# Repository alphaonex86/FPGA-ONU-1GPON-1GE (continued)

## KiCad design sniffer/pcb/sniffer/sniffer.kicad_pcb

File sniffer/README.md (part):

# GPON sniffer

A passive tap on one ONU's drop fibre: both directions of that ONU's GPON traffic,
filtered to what concerns it, dumped with the direction of every record. Simple and
cheap: one small card on the DE25-Nano 40-pin GPIO. Origin: `../common/sniffer/sniffer-GPON.jpg`.

Versus the FPGA ONU (operator, 2026-11-02): the ONU + OLT proxy of this repo sits in the path
and can intervene in the packets; the sniffer cannot touch anything, it only listens, but it
dumps without complications (no activation, no cloning, the stock ONU keeps its link).

## Decisions (operator, 2026-11-02)

- Customer side, not provider: the OLT is the ISP's, remote and out of our hands. The tap goes
  between the wall fibre outlet and our own ONU; the sniffer must stay invisible to the ISP
  (passive, never emits; our ONU receives about 4 dB less, see Coupler).
- The link: about 5 km of fibre from the ISP; our ONU reports
  -17 to -27 dBm received. -27 dBm is already at a class B+ ONU's sensitivity (-27/-28 dBm),
  so any optical tap that takes light from the downstream can drop our ONU off the PON.
  Range across installations: the sniffer is for homes at -23 dBm or better (Coupler).
- Tap: two 1x2 couplers back to back in our ONU's drop (Coupler below), so the two
  directions arrive on two fibres (no WDM) and the upstream holds our ONU's bursts only,
  at one constant power.
- Optics: two BOSAs, receive only. Downstream: an ONU BOSA RX (X100DG, 1490 nm, APD-TIA).
  Upstream: the OLT BOSA XL-BCB2111-LS-02 RX (1310 nm, 1.25 Gb/s APD-TIA, -32 dBm). Each
  into a SY88349NDL limiting amp. No laser driver is fitted: the sniffer cannot emit into
  the PON, by construction. SFP modules were dropped: no raw GPON ONU module without a MAC
  on AliExpress (only "sticks" with a MAC); raw ones exist at Optcore/FiberMall/PLANET.
- Platform: an ECP5 SerDes card on the DE25-Nano GPIO (the `../de25-nano/pcb` bridge
  plan; the operator owns a DE25-Nano). The ECP5 deserialises; the Agilex runs the existing GTC deframer, FEC, AES
  and the filter; the HPS writes the dump.

## Coupler (operator, 2026-11-02)

Two 1x2 back to back: wall - [common 1x2 #1 50 %] - [90 % 1x2 #2 common] - ONU. The free leg of #1
is the downstream copy, the 10 % leg of #2 the upstream copy (one 1x2 alone taps one direction:
the light entering a leg leaves by the common port). #1 is a 50:50, #2 a 90:10: the
operator has several of each (unbalanced 1x2 for building GPON networks).
- ONU: about 4 dB less (3.5 + 0.5). The -17 to -27 dBm range is across installations, so the
  sniffer fits a home whose ONU reports -23 dBm or better without the tap (it then stays at
  -27 dBm or better, a class B+ ONU's sensitivity).
- Downstream: the sniffer gets the ONU's tapped level + 0.5 dB, at least -26.5 dBm there, above
  the APD's -28 dBm.
- Upstream: the ONU emits +0.5 to +5 dBm, the sniffer sees about -10 to -5.5 dBm, near an APD's
  overload (-8 dBm typical for an OLT receiver): a 5 dB SC attenuator on the upstream tap fibre.

## DE25-Nano: verified (2026-11-02)

- GPIO headers are 3.3 V HVIO: 100 MHz SDR or 200 Mb/s DDR per pin (Altera Agilex 5 GPIO
  architecture brief); the HVIO clock input reaches the I/O PLL up to 156.25 MHz (data sheet).
- So the card sends DDR: DS 2.48832 Gb/s on 16 pins + US 1.24416 Gb/s on 8 pins, 155.52 Mb/s
  per pin (78 % of the limit) on a 77.76 MHz forwarded clock. With CCLK/MOSI/MISO/SN/PROGRAMN
  (slave-SPI configuration from the Agilex) and I2C: 36 of the 40 pins of GPIO_0.
- The Agilex A5EB013 is the DE25-Standard's density (138K LE), where the GTC/FEC/AES already
  meet timing; the HPS has the GbE port and the microSD for the dump.
- The two ECP5 bridge boards in `../de25-nano/pcb` send 155.52 MHz SDR: above the 100 MHz HVIO limit.

## Card (`pcb/sniffer`, generated by `../common/pcb/gen`)

Routed 2026-11-02: KRT, then close_opens on the last 5 nets; KiCad: 0 errors, 0 unconnected.

ECP5 LFE5UM-25F (as the bridge boards), SerDes RX only: CH0 downstream (CDR), CH1 upstream
(lock-to-reference on the 155.52 MHz VCXO, which the ECP5 locks to the downstream like the
ONU board, so each burst needs only a phase pick). Each BOSA: receive can only, into a
SY88349NDL burst-mode limiting amp (SD mode, auto reset, squelch), its own TPS61391 APD bias
(DAC trim from an AD5593R, which also reads both APD currents = optical power at the tap).
Upstream coupling 220 pF (tau 11 ns), downstream 100 nF.

## Filter (downstream; the upstream is already this ONU only)

The ONU is named by its serial number. From the PLOAMs: Assign_ONU-ID (serial ->
ONU-ID), Assign_Alloc-ID, Configure_Port-ID (OMCI); from OMCI: the GEM Port CTPs
(data Port-IDs). Kept: PLOAMs to that ONU-ID or broadcast, the BWmap entries of its
Alloc-IDs, the GEM frames of its Port-IDs.

## RTL (`../common/hw/spinal/pon/sniffer`, test `pon.sniffer.SnifferTest`)

Vendor-neutral SpinalHDL, one line byte per clock per direction; no AES in hardware.
- `SnifferDs` (311.04 MHz): the GTC deframer (FEC included), then the filter: PLOAMs to
  `onuId` or broadcast (all with `allPloams`), BWmap entries and GEM fragments by two
  4096-bit maps (Alloc-ID, Port-ID) the HPS writes. GEM stays ciphered; its record carries
  the crypto-counter, the software decrypts.
- `SnifferUs` (155.52 MHz): delimiter hunt on any bit alignment, descramble from the BIP,
  one record per burst until 8 squelched (zero) line bytes.
- `RecordWriter`: the record stream; a record is kept or dropped whole, a full data FIFO
  cuts its tail (flag bit 7); drop and truncation counters.

Record: `0xA0|kind`, flags, payload length (16 LE), time (64 LE), payload.

| kind | payload | flags |
|------|---------|-------|
| 0 PLOAM | 12 bytes | 0: bad CRC |
| 1 allocation | 7 bytes as on the line | 0: bad CRC |
| 2 GEM fragment | Port-ID 16, PLI 16, counter 48, data | 2..0: PTI, 3: cut, 4: first bytes only (dump rule) |
| 3 upstream burst | BIP, ONU-ID, Ind, allocations | 0: maxBytes reached, 1: filtered, 2: FEC parity left out |

A filtered burst (in-line box, dump rules: `DumpRules.scala`, `UsGemFilter`) ends with its line length (16 LE); a
GEM fragment a rule dropped or shortened keeps its header, the HEC field XORed with `0x1000 | payload bytes left`.
Of a run of idle GEM headers the last one stays, its HEC field XORed with `0x1000 | idle headers left out before it`
(none left out: unchanged).

ECP5 (`ecp5/`, `sh sniffer/ecp5/build.sh` -> `out/ecp5/sniffer.bit`, yosys + nextpnr + trellis):
`sniffer_ecp5.v` (DCU, resets, PLL, DDR pins) around `SnifferBridge` (test `pon.sniffer.SnifferBridgeTest`);
`gen.py` writes the DCU parameters and the LPF from the routed board. All in the VCXO's domain
(124.416 MHz, CH0's TX clock): CH1 is read there; the downstream crosses a 16-word FIFO whose
fill is the phase detector of the VCXO loop (PI every 132 us, sigma-delta on VCXO_PWM;
`ecp5/vcxo_loop_model.py`: locked to 0.5 word in 14 s from 10 ppm). Upstream: one sample per
pair, the centre of isolated 1- or 3-sample runs (an edge on a sample reads either bit).
Timing (speed 6): VCXO domain 135.6 MHz for 124.4, out 125 for 77.8, DS 255 for 124.4.

Still to write: the Agilex wrapper (DDR capture, x4 / x2 serialisers, time base, both
streams to the HPS).

## Dump

pcapng, one interface per direction (0 = downstream, 1 = upstream), hardware
timestamps; one packet per record.

## Open

- SY88349NDL stock (LCSC not reachable from here) and its SD level resistor (5.1k start).
- Lead order of the X100DG BOSA's RX can (to measure); XL-BCB2111 order from its drawing.
- XL-BCB2111 connector: SC/UPC in the title, SC/APC on the drawing.
- CH1 between bursts: with the line squelched the DCU sees LOS and its phase detector stops
  (`PDEN_SEL`); the 2x pick needs the DCO to stay on the reference frequency there, to measure.
- DCU bit order: the first received bit taken in D0 (as LiteICLink's 8b10b path); a reversed
  lane would show as a deframer that never syncs.
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
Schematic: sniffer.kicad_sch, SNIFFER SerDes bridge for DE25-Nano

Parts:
C1, C3, C6, C9, C24, C25, C30, C48, C49, C50, C51, C54, C57, C60, C63, C65, C71, C80, C87, C96: 10u; C_0603_1608Metric
C2, C4, C5, C7, C8, C10, C11: 22u; C_0805_2012Metric
C12, C13, C66, C67: 1u; C_0402_1005Metric
C14, C15, C16, C17, C18, C19, C20, C21, C22, C23, C26, C27, C28, C29, C31, C32, C33, C34, C35, C36, C37, C38, C39, C40, C41, C42, C43, C44, C45, C46, C47, C52, C53, C55, C56, C58, C59, C61, C62, C64, C68, C69, C70, C72, C73, C74, C75, C76, C77, C78, C79, C83, C84, C85, C86, C95, C104, C105: 100n; C_0402_1005Metric
C81, C82: 220p; C_0402_1005Metric
C88, C89, C97, C98: 100n; C_0603_1608Metric; MPN 100 V X7R
C90, C99: 220p; C_0603_1608Metric; MPN 100 V X7R
C91, C100: 10n; C_0402_1005Metric; MPN 100 V X7R
C92, C101: 2.2u; C_0603_1608Metric
C93, C94, C102, C103: 10p; C_0402_1005Metric
D1, D2: BAT46WJ; D_SOD-323F; MPN BAT46WJ (100 V)
FB1, FB2, FB3, FB4, FB5, FB6, FB7, FB8, FB9, FB10: 120R@100MHz; L_0603_1608Metric; MPN BLM18PG121SN1D
H1, H2: M3; MountingHole_3.2mm_M3
J1: DE25-Nano GPIO; PinSocket_2x20_P2.54mm_Vertical
J2: JTAG; PinHeader_1x06_P2.54mm_Vertical
L1, L2: 2.2u; L_Cenker_CKCS252012; MPN SLO252012F2R2MTT
L3, L4: 4.7u; L_Cenker_CKCS252012; MPN 4.7 uH, Isat >= 1 A, 2520
R1, R3: 100k; R_0402_1005Metric
R2, R4: 120k; R_0402_1005Metric
R5, R6, R7, R8, R9, R12, R13, R14, R20, R24: 4.7k; R_0402_1005Metric
R10, R15, R16, R28, R37, R43, R46: 10k; R_0402_1005Metric
R11, R26, R35: 1k; R_0402_1005Metric
R17, R18, R21, R22: 49.9; R_0402_1005Metric
R19, R23: 5.1k; R_0402_1005Metric
R25, R34: 100; R_0402_1005Metric
R27: 300k; R_0603_1608Metric
R29, R38: 20k; R_0402_1005Metric
R30, R39: 39k; R_0402_1005Metric
R31, R40: 10; R_0402_1005Metric
R32, R41: 1.5k; R_0402_1005Metric
R33, R42: 3.01k; R_0402_1005Metric
R36: 330k; R_0603_1608Metric
R44, R45: 2.2k; R_0402_1005Metric
RN1, RN2, RN3, RN4, RN5, RN6, RN7: 22; R_Array_Convex_4x0402; MPN 4D02WGJ0220TCE
U1, U2: TLV62569DBVR; SOT-23-5; MPN TLV62569DBVR
U3: TLV75525PDBVR; SOT-23-5; MPN TLV75525PDBVR
U4: LFE5UM-25F-6BG381C; Lattice_caBGA-381_17x17mm_Layout20x20_P0.8mm; MPN LFE5UM-25F-6BG381C
U5: BOSA GPON (X100DG), RX can only; BOSA_GPON
U6, U8: SY88349NDLMG; QFN-16-1EP_3x3mm_P0.5mm_EP1.7x1.7mm_ThermalVias; MPN SY88349NDLMG
U7: XL-BCB2111-LS-02, RX can only; BOSA_RX_TO46
U9, U10: TPS61391RTER; WQFN-16-1EP_3x3mm_P0.5mm_EP1.68x1.68mm_ThermalVias; MPN TPS61391RTER
U11: AD5593RBRUZ; TSSOP-16_4.4x5mm_P0.65mm; MPN AD5593RBRUZ
Y1: SiT3821 155.52 MHz; Oscillator_SMD_SiTime_SiT9121-6Pin_3.2x2.5mm; MPN SiT3821AI-2B2-33NB155.520000 (LVDS, +-5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

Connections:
+1V1: C7.1, C8.1, C14.1, C15.1, C16.1, C17.1, C18.1, C19.1, C20.1, C21.1, C22.1, C23.1, C24.1, C25.1, L1.2, R1.1, U4.H8 (VCC), U4.H9 (VCC), U4.H10 (VCC), U4.H11 (VCC), U4.H12 (VCC), U4.H13 (VCC), U4.J8 (VCC), U4.J13 (VCC), U4.K8 (VCC), U4.K13 (VCC), U4.L8 (VCC), U4.L13 (VCC), U4.M8 (VCC), U4.M13 (VCC), U4.N8 (VCC), U4.N9 (VCC), U4.N10 (VCC), U4.N11 (VCC), U4.N12 (VCC), U4.N13 (VCC)
+1V1_HRX: C58.1, C59.1, C60.1, FB4.2, U4.T8 (VCCHRX0_D0CH0), U4.T9 (VCCHRX1_D0CH1)
+1V1_HTX: C55.1, C56.1, C57.1, FB3.2, U4.T7 (VCCHTX0_D0CH0), U4.T10 (VCCHTX1_D0CH1)
+1V1_SD: C10.1, C11.1, FB2.1, FB3.1, FB4.1, L2.2, R3.1
+1V1_VCCA: C52.1, C53.1, C54.1, FB2.2, U4.T6 (VCCA0), U4.U6 (VCCA0)
+2V5: C13.1, FB1.1, FB5.1, U3.5 (OUT)
+2V5_AUX: C26.1, C27.1, C28.1, C29.1, C30.1, FB1.2, U4.F6 (VCCAUX), U4.F15 (VCCAUX), U4.P6 (VCCAUX), U4.P15 (VCCAUX)
+2V5_AUXA: C61.1, C62.1, C63.1, FB5.2, U4.V10 (VCCAUXA0), U4.V11 (VCCAUXA0)
+3V3: C3.1, C4.1, C5.1, C12.1, C31.1, C32.1, C33.1, C34.1, C35.1, C36.1, C37.1, C38.1, C39.1, C40.1, C41.1, C42.1, C43.1, C44.1, C45.1, C46.1, C47.1, C48.1, C49.1, C50.1, C51.1, C105.1, FB6.1, FB7.1, FB8.1, FB9.1, FB10.1, J1.29, J2.1, R5.2, R6.2, R7.2, R8.2, R9.2, R10.2, R11.2, R12.2, R13.2, R20.2, R24.2, R43.2, R44.2, R45.2, R46.2, U3.1 (IN), U3.3 (EN), U4.F9 (VCCIO0), U4.F10 (VCCIO0), U4.F11 (VCCIO1), U4.F12 (VCCIO1), U4.H6 (VCCIO7), U4.H7 (VCCIO7), U4.H14 (VCCIO2), U4.H15 (VCCIO2), U4.J6 (VCCIO7), U4.J15 (VCCIO2), U4.L6 (VCCIO6), U4.L7 (VCCIO6), U4.L14 (VCCIO3), U4.L15 (VCCIO3), U4.M6 (VCCIO6), U4.M15 (VCCIO3), U4.P9 (VCCIO8), U4.P10 (VCCIO8), U11.3 (V_{DD}), U11.9 (V_{LOGIC})
+3V3_DS_APD: C86.1, C87.1, FB9.2, L3.1, R31.1, U9.10 (VIN), U9.13 (EN)
+3V3_DS_APDA: C92.1, R31.2, U9.14 (AVCC), U9.15 (AVCC)
+3V3_DS_OPT: C68.1, C69.1, C70.1, C71.1, FB7.2, R19.2, U5.R2 (VCC), U6.5 (VCC), U6.13 (LOS/SD_SEL), U6.16 (VCC)
+3V3_US_APD: C95.1, C96.1, FB10.2, L4.1, R40.1, U10.10 (VIN), U10.13 (EN)
+3V3_US_APDA: C101.1, R40.2, U10.14 (AVCC), U10.15 (AVCC)
+3V3_US_OPT: C77.1, C78.1, C79.1, C80.1, FB8.2, R23.2, U7.1 (VCC), U8.5 (VCC), U8.13 (LOS/SD_SEL), U8.16 (VCC)
+3V3_XO: C64.1, C65.1, FB6.2, Y1.6 (VDD)
+5V: C1.1, C2.1, C6.1, C9.1, J1.11, U1.1 (EN), U1.4 (VIN), U2.1 (EN), U2.4 (VIN)
CCLK: J1.15, R11.1, U4.U3 (CCLK)
CFG0: R5.1, U4.U4 (CFG_0)
DDM_RESET: R43.1, U11.1 (~RESET)
DDM_VREF: C104.1, U11.8 (V_{REF})
DONE: R8.1, U4.Y3 (DONE)
DS0: J1.13, RN4.5 (R4.2)
DS0_S: RN4.4 (R4.1), U4.B12 (PT35A/PCLKT1_0)
DS1: J1.14, RN4.6 (R3.2)
DS1_S: RN4.3 (R3.1), U4.B11 (PT29A/PCLKT0_0)
DS2: J1.16, RN4.7 (R2.2)
DS2_S: RN4.2 (R2.1), U4.A11 (PT27B/PCLKC0_1)
DS3: J1.18, RN4.8 (R1.2)
DS3_S: RN4.1 (R1.1), U4.A10 (PT27A/PCLKT0_1)
DS4: J1.23, RN3.5 (R4.2)
DS4_S: RN3.4 (R4.1), U4.B9 (PT22A)
DS5: J1.27, RN3.6 (R3.2)
DS5_S: RN3.3 (R3.1), U4.A9 (PT24A/GR_PCLK0_1)
DS6: J1.28, RN3.7 (R2.2)
DS6_S: RN3.2 (R2.1), U4.A8 (PT18B)
DS7: J1.31, RN3.8 (R1.2)
DS7_S: RN3.1 (R1.1), U4.A7 (PT18A)
DS8: J1.32, RN2.5 (R4.2)
DS8_S: RN2.4 (R4.1), U4.A6 (PT4A)
DS9: J1.33, RN2.6 (R3.2)
DS9_S: RN2.3 (R3.1), U4.B5 (PL2C)
DS10: J1.34, RN2.7 (R2.2)
DS10_S: RN2.2 (R2.1), U4.A5 (PL2B)
DS11: J1.35, RN2.8 (R1.2)
DS11_S: RN2.1 (R1.1), U4.A4 (PL2A)
DS12: J1.36, RN1.5 (R4.2)
DS12_S: RN1.4 (R4.1), U4.B3 (PL5D)
DS13: J1.37, RN1.6 (R3.2)
DS13_S: RN1.3 (R3.1), U4.B2 (PL14C/VREF1_7)
DS14: J1.38, RN1.7 (R2.2)
DS14_S: RN1.2 (R2.1), U4.A2 (PL14A)
DS15: J1.39, RN1.8 (R1.2)
DS15_S: RN1.1 (R1.1), U4.B1 (PL14B)
DS_APD_ADJ: R29.2, U11.4 (IO0)
DS_APD_CAP: C91.1, U9.9 (CAP)
DS_APD_FB: R27.2, R28.1, R29.1, U9.12 (FB)
DS_APD_ISHORT: R30.1, U9.11 (ISHORT)
DS_APD_MON: C93.1, R32.1, U9.4 (MON1), U11.6 (IO2)
DS_APD_MON2: C94.1, R33.1, U9.3 (MON2)
DS_DIN_N: C73.2, R18.1, U6.4 (/DIN)
DS_DIN_P: C72.2, R17.1, U6.1 (DIN)
DS_HV_APD: C90.1, U5.R1 (VAPD), U9.5 (APD)
DS_HV_FILT: C89.1, R25.2, R26.1
DS_HV_MONIN: R26.2, U9.6 (MONIN)
DS_HV_OUT: C88.1, D1.1 (K), R25.1, R27.1
DS_HV_SW: D1.2 (A), L3.2, U9.8 (SW)
DS_LA_N: C76.1, U6.9 (/DOUT)
DS_LA_P: C75.1, U6.12 (DOUT)
DS_RX_N: C76.2, U4.Y6 (HDRXN0_D0CH0)
DS_RX_P: C75.2, U4.Y5 (HDRXP0_D0CH0)
DS_SD: R20.1, U4.U17 (PR47B), U6.7 (SD/LOS), U6.15 (JAM)
DS_SDLVL: R19.1, U6.14 (LOS/SDLVL)
DS_TIA_N: C73.1, U5.R4 (OUT-)
DS_TIA_P: C72.1, U5.R3 (OUT+)
DS_VREF: C74.1, R17.2, R18.2, U6.2 (VREF)
FB_1V1: R1.2, R2.1, U1.5 (FB)
FB_1V1_SD: R3.2, R4.1, U2.5 (FB)
FWD_CLK: J1.1, RN7.8 (R1.2)
FWD_CLK_S: RN7.1 (R1.1), U4.B19 (PT65B)
GND: C1.2, C2.2, C3.2, C4.2, C5.2, C6.2, C7.2, C8.2, C9.2, C10.2, C11.2, C12.2, C13.2, C14.2, C15.2, C16.2, C17.2, C18.2, C19.2, C20.2, C21.2, C22.2, C23.2, C24.2, C25.2, C26.2, C27.2, C28.2, C29.2, C30.2, C31.2, C32.2, C33.2, C34.2, C35.2, C36.2, C37.2, C38.2, C39.2, C40.2, C41.2, C42.2, C43.2, C44.2, C45.2, C46.2, C47.2, C48.2, C49.2, C50.2, C51.2, C52.2, C53.2, C54.2, C55.2, C56.2, C57.2, C58.2, C59.2, C60.2, C61.2, C62.2, C63.2, C64.2, C65.2, C66.2, C67.2, C68.2, C69.2, C70.2, C71.2, C74.2, C77.2, C78.2, C79.2, C80.2, C83.2, C86.2, C87.2, C88.2, C89.2, C90.2, C91.2, C92.2, C93.2, C94.2, C95.2, C96.2, C97.2, C98.2, C99.2, C100.2, C101.2, C102.2, C103.2, C104.2, C105.2, J1.12, J1.30, J2.6, R2.2, R4.2, R14.2, R28.2, R30.2, R32.2, R33.2, R37.2, R39.2, R41.2, R42.2, U1.2 (GND), U2.2 (GND), U3.2 (GND)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
HOLDN: R10.1, U4.R2 (PB15A/HOLDN/DI/BUSY/CSSPIN/CEN)
INITN: R7.1, U4.V3 (INITN)
MISO: J1.19, R46.1, U4.V2 (PB11A/D1/MISO/IO1)
MOSI: J1.17, U4.W2 (PB11B/D0/MOSI/IO0)
PROGRAMN: J1.20, R6.1, U4.W3 (PROGRAMN)
REFCLK_N: U4.Y12 (REFCLKN_D0), Y1.5 (OUT-)
REFCLK_P: U4.Y11 (REFCLKP_D0), Y1.4 (OUT+)
SCL: J1.21, R44.1, U11.16 (SCL)
SDA: J1.22, R45.1, U11.15 (SDA)
SN: J1.40, R9.1, U4.T2 (PB13A/SN/CSN)
SW_1V1: L1.1, U1.3 (SW)
SW_1V1_SD: L2.1, U2.3 (SW)
TCK: J2.2, R14.1, U4.T5 (TCK)
TDI: J2.3, R12.1, U4.R5 (TDI)
TDO: J2.4, U4.V4 (TDO)
TMS: J2.5, R13.1, U4.U5 (TMS)
US0: J1.2, RN6.5 (R4.2)
US0_S: RN6.4 (R4.1), U4.A19 (PT67A)
US1: J1.4, RN6.6 (R3.2)
US1_S: RN6.3 (R3.1), U4.A18 (PT65A)
US2: J1.5, RN6.7 (R2.2)
US2_S: RN6.2 (R2.1), U4.B17 (PT60A)
US3: J1.6, RN6.8 (R1.2)
US3_S: RN6.1 (R1.1), U4.A17 (PT62A)
US4: J1.7, RN5.5 (R4.2)
US4_S: RN5.4 (R4.1), U4.A16 (PT56A)
US5: J1.8, RN5.6 (R3.2)
US5_S: RN5.3 (R3.1), U4.B15 (PT51A)
US6: J1.9, RN5.7 (R2.2)
US6_S: RN5.2 (R2.1), U4.B13 (PT42A)
US7: J1.10, RN5.8 (R1.2)
US7_S: RN5.1 (R1.1), U4.A13 (PT40B)
US_APD_ADJ: R38.2, U11.5 (IO1)
US_APD_CAP: C100.1, U10.9 (CAP)
US_APD_FB: R36.2, R37.1, R38.1, U10.12 (FB)
US_APD_ISHORT: R39.1, U10.11 (ISHORT)
US_APD_MON: C102.1, R41.1, U10.4 (MON1), U11.7 (IO3)
US_APD_MON2: C103.1, R42.1, U10.3 (MON2)
US_DIN_N: C82.2, R22.1, U8.4 (/DIN)
US_DIN_P: C81.2, R21.1, U8.1 (DIN)
US_HV_APD: C99.1, U7.2 (VAPD), U10.5 (APD)
US_HV_FILT: C98.1, R34.2, R35.1
US_HV_MONIN: R35.2, U10.6 (MONIN)
US_HV_OUT: C97.1, D2.1 (K), R34.1, R36.1
US_HV_SW: D2.2 (A), L4.2, U10.8 (SW)
US_LA_N: C85.1, U8.9 (/DOUT)
US_LA_P: C84.1, U8.12 (DOUT)
US_RX_N: C85.2, U4.Y8 (HDRXN0_D0CH1)
US_RX_P: C84.2, U4.Y7 (HDRXP0_D0CH1)
US_SD: R24.1, U4.T17 (PR47D/LRC_GPLL0C_IN), U8.7 (SD/LOS), U8.15 (JAM)
US_SDLVL: R23.1, U8.14 (LOS/SDLVL)
US_TIA_N: C82.1, U7.3 (OUT-)
US_TIA_P: C81.1, U7.5 (OUT+)
US_VREF: C83.1, R21.2, R22.2, U8.2 (VREF)
VCXO_PWM: R15.1, U4.U16 (PR47C/LRC_GPLL0T_IN)
VCXO_RC: C66.1, R15.2, R16.1
VCXO_VC: C67.1, R16.2, Y1.1 (VIN)

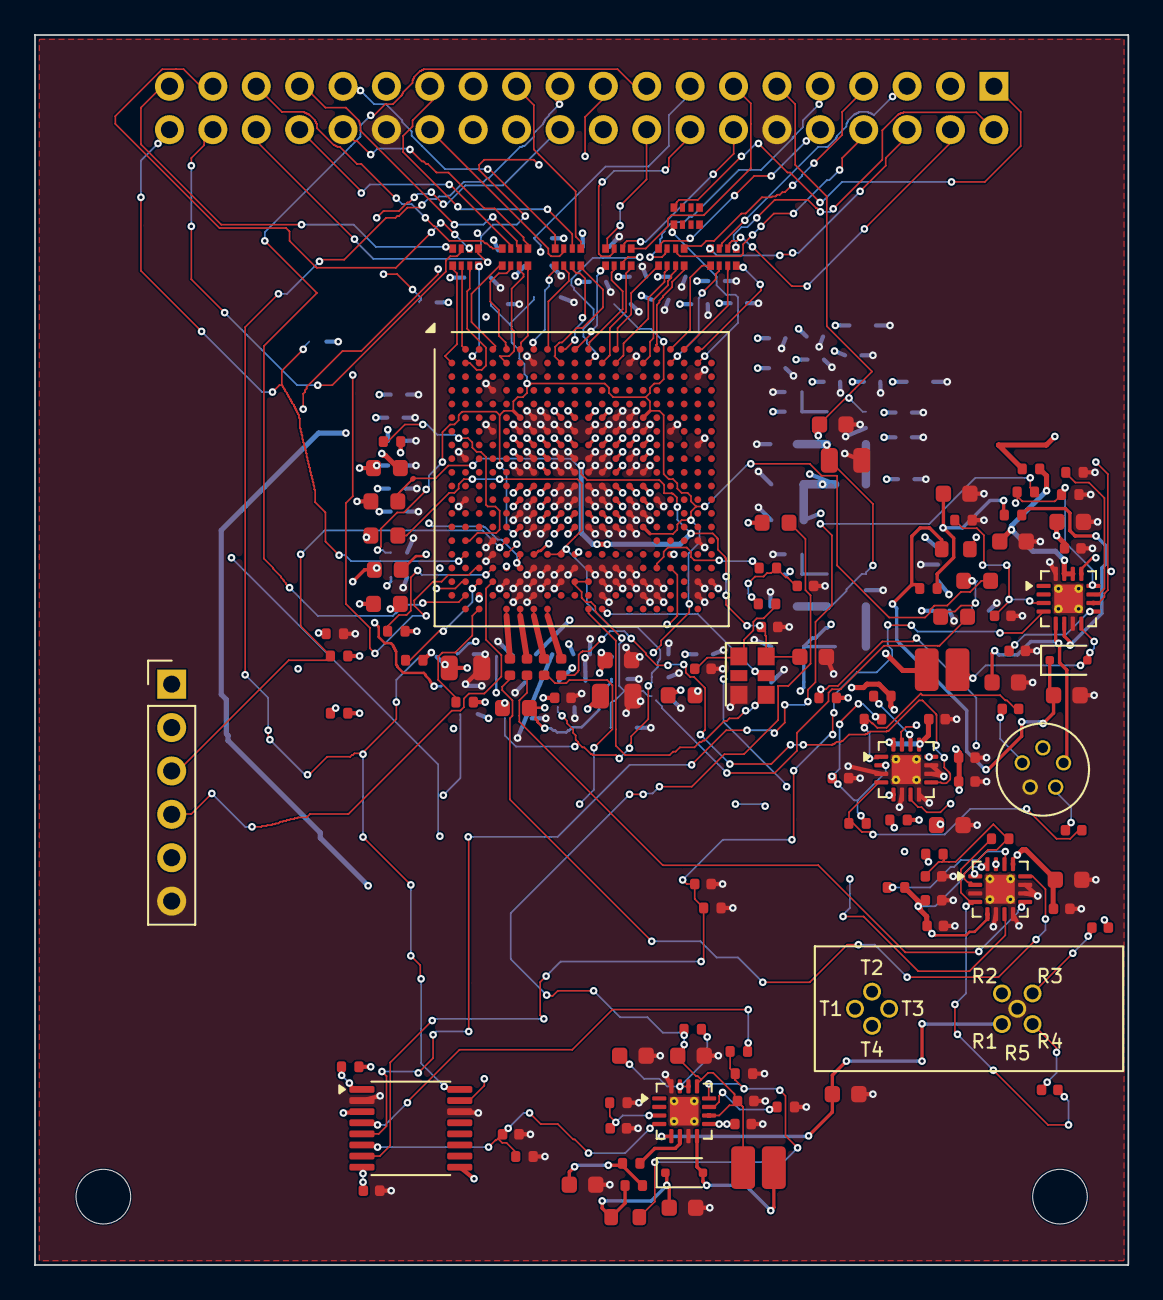
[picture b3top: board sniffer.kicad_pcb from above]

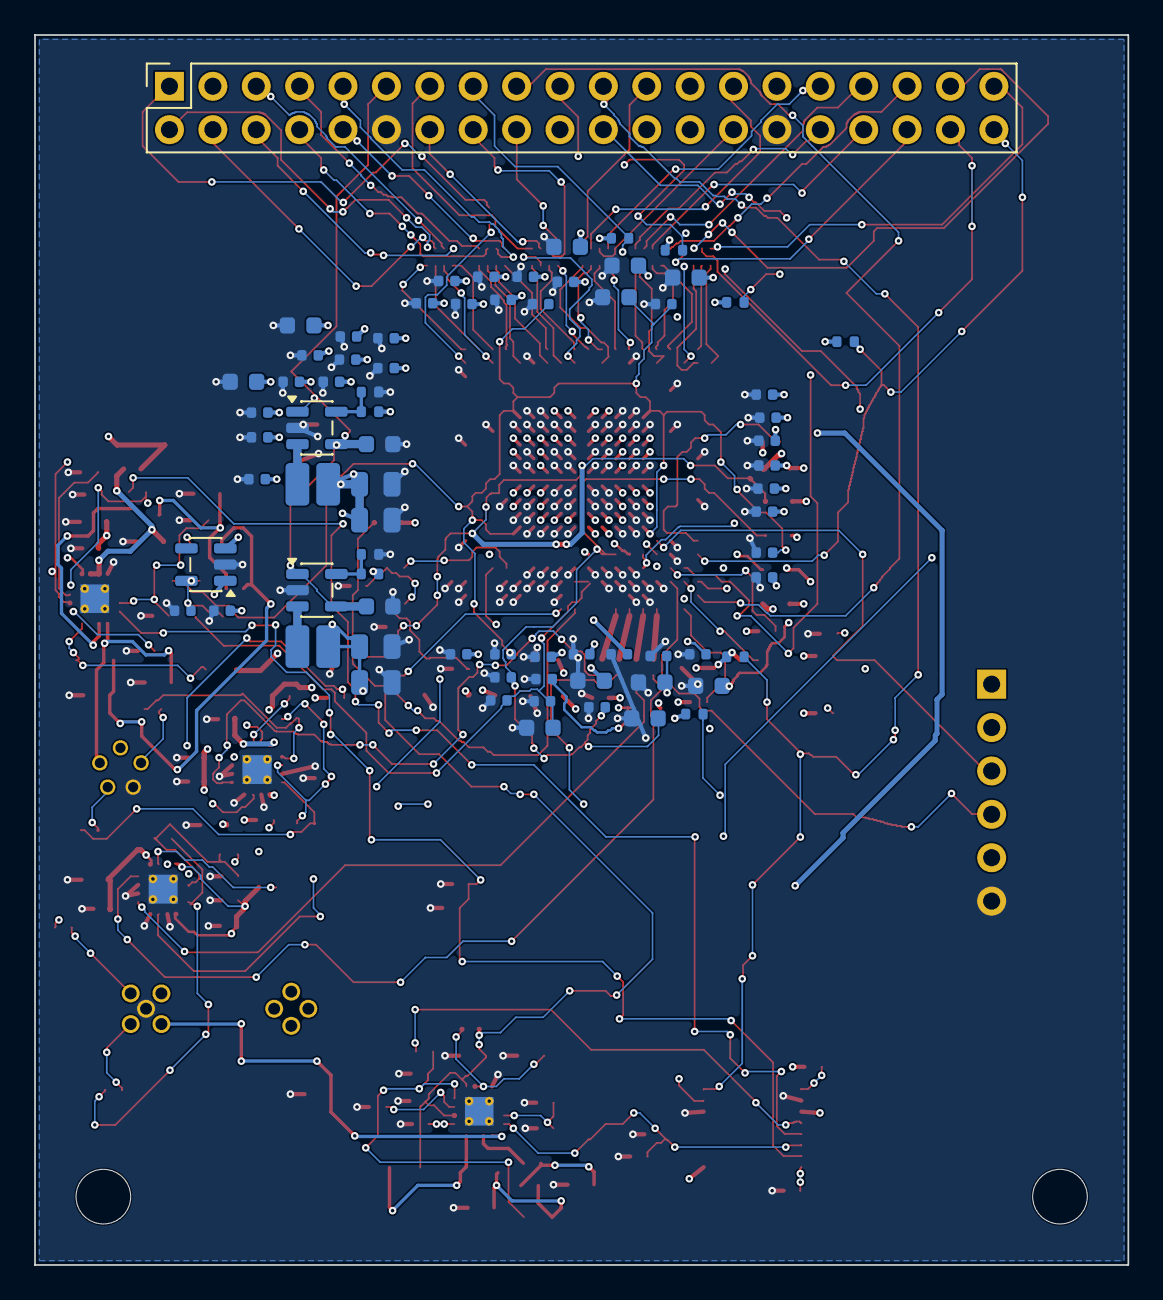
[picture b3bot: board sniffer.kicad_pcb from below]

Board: 4 copper layers, 64.0 x 72.0 mm, 190 parts (74 on the bottom side), 138 nets.

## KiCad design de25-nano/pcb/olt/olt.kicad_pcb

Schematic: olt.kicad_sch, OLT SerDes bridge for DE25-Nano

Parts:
C1, C3, C6, C9, C24, C25, C30, C48, C49, C50, C51, C54, C57, C60, C63, C66, C72, C74: 10u; C_0603_1608Metric
C2, C4, C5, C7, C8, C10, C11, C75: 22u; C_0805_2012Metric
C12, C13: 1u; C_0402_1005Metric
C14, C15, C16, C17, C18, C19, C20, C21, C22, C23, C26, C27, C28, C29, C31, C32, C33, C34, C35, C36, C37, C38, C39, C40, C41, C42, C43, C44, C45, C46, C47, C52, C53, C55, C56, C58, C59, C61, C62, C64, C65, C67, C68, C69, C70, C71, C73: 100n; C_0402_1005Metric
FB1, FB2, FB3, FB4, FB5, FB6: 120R@100MHz; L_0603_1608Metric; MPN BLM18PG121SN1D
H1, H2: M3; MountingHole_3.2mm_M3
J1: DE25-Nano GPIO; PinSocket_2x20_P2.54mm_Vertical
J2: JTAG; PinHeader_1x06_P2.54mm_Vertical
J3: SFP cage; Connector_SFP_and_Cage; MPN TE 1367073-1 + cage 2227302-1
J4: OLT-ONU link; PinHeader_1x08_P2.54mm_Vertical
L1, L2: 2.2u; L_Cenker_CKCS252012; MPN SLO252012F2R2MTT
L3, L4: 1u; L_0805_2012Metric; MPN 1 uH >= 1 A, low DCR
R1, R3: 100k; R_0402_1005Metric
R2, R4: 120k; R_0402_1005Metric
R5, R6, R7, R8, R9, R12, R13, R14, R21, R22, R27, R28, R29, R30, R31, R32: 4.7k; R_0402_1005Metric
R10, R15, R16, R17, R20, R23, R24: 10k; R_0402_1005Metric
R11: 1k; R_0402_1005Metric
R18, R19: 2.2k; R_0402_1005Metric
R25: 33; R_0402_1005Metric
R26: 330; R_0402_1005Metric
RN1, RN2, RN3: 22; R_Array_Convex_4x0402; MPN 4D02WGJ0220TCE
U1, U2: TLV62569DBVR; SOT-23-5; MPN TLV62569DBVR
U3: TLV75525PDBVR; SOT-23-5; MPN TLV75525PDBVR
U4: LFE5UM-25F-6BG381C; Lattice_caBGA-381_17x17mm_Layout20x20_P0.8mm; MPN LFE5UM-25F-6BG381C
U5: PCA9555PW; TSSOP-24_4.4x7.8mm_P0.65mm; MPN PCA9555PW
U6: PCA9540BD; SOIC-8_3.9x4.9mm_P1.27mm; MPN PCA9540BD
U7, U8: SN74LVC1G125DBVR; SOT-23-5; MPN SN74LVC1G125DBVR
Y1: SiT9121 155.52 MHz; Oscillator_SMD_SiTime_SiT9121-6Pin_3.2x2.5mm; MPN SiT9121AI-2B3-33E155.52000 (LVDS; check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
Y2: SiT9121 125 MHz; Oscillator_SMD_SiTime_SiT9121-6Pin_3.2x2.5mm; MPN SiT9121AI-2B3-33E125000 (LVDS; check co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

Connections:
+1V1: C7.1, C8.1, C14.1, C15.1, C16.1, C17.1, C18.1, C19.1, C20.1, C21.1, C22.1, C23.1, C24.1, C25.1, L1.2, R1.1, U4.H8 (VCC), U4.H9 (VCC), U4.H10 (VCC), U4.H11 (VCC), U4.H12 (VCC), U4.H13 (VCC), U4.J8 (VCC), U4.J13 (VCC), U4.K8 (VCC), U4.K13 (VCC), U4.L8 (VCC), U4.L13 (VCC), U4.M8 (VCC), U4.M13 (VCC), U4.N8 (VCC), U4.N9 (VCC), U4.N10 (VCC), U4.N11 (VCC), U4.N12 (VCC), U4.N13 (VCC)
+1V1_HRX: C58.1, C59.1, C60.1, FB4.2, U4.T8 (VCCHRX0_D0CH0)
+1V1_HTX: C55.1, C56.1, C57.1, FB3.2, U4.T7 (VCCHTX0_D0CH0), U4.T10 (VCCHTX1_D0CH1)
+1V1_SD: C10.1, C11.1, FB2.1, FB3.1, FB4.1, L2.2, R3.1
+1V1_VCCA: C52.1, C53.1, C54.1, FB2.2, U4.T6 (VCCA0), U4.U6 (VCCA0)
+2V5: C13.1, FB1.1, FB5.1, U3.5 (OUT)
+2V5_AUX: C26.1, C27.1, C28.1, C29.1, C30.1, FB1.2, U4.F6 (VCCAUX), U4.F15 (VCCAUX), U4.P6 (VCCAUX), U4.P15 (VCCAUX)
+2V5_AUXA: C61.1, C62.1, C63.1, FB5.2, U4.V10 (VCCAUXA0), U4.V11 (VCCAUXA0)
+3V3: C3.1, C4.1, C5.1, C12.1, C31.1, C32.1, C33.1, C34.1, C35.1, C36.1, C37.1, C38.1, C39.1, C40.1, C41.1, C42.1, C43.1, C44.1, C45.1, C46.1, C47.1, C48.1, C49.1, C50.1, C51.1, C67.1, C68.1, C69.1, C70.1, C75.1, FB6.1, J1.29, J2.1, L3.1, L4.1, R5.2, R6.2, R7.2, R8.2, R9.2, R10.2, R11.2, R12.2, R13.2, R15.2, R16.2, R18.2, R19.2, R20.2, R21.2, R22.2, R23.2, R24.2, R27.2, R28.2, R29.2, R30.2, R31.2, R32.2, U3.1 (IN), U3.3 (EN), U4.F9 (VCCIO0), U4.F10 (VCCIO0), U4.F11 (VCCIO1), U4.F12 (VCCIO1), U4.H6 (VCCIO7), U4.H7 (VCCIO7), U4.H14 (VCCIO2), U4.H15 (VCCIO2), U4.J6 (VCCIO7), U4.J15 (VCCIO2), U4.L6 (VCCIO6), U4.L7 (VCCIO6), U4.L14 (VCCIO3), U4.L15 (VCCIO3), U4.M6 (VCCIO6), U4.M15 (VCCIO3), U4.P9 (VCCIO8), U4.P10 (VCCIO8), U5.24 (VDD), U6.3 (VDD), U7.5 (VCC), U8.5 (VCC)
+3V3_SFPR: C73.1, C74.1, J3.15 (VccR), L4.2
+3V3_SFPT: C71.1, C72.1, J3.16 (VccT), L3.2
+3V3_XO: C64.1, C65.1, C66.1, FB6.2, Y1.6 (VDD), Y2.6 (VDD)
+5V: C1.1, C2.1, C6.1, C9.1, J1.11, U1.1 (EN), U1.4 (VIN), U2.1 (EN), U2.4 (VIN)
AUX: J1.16, RN1.8 (R1.2)
AUX_S: RN1.1 (R1.1), U4.A10 (PT27A/PCLKT0_1)
CCLK: J1.37, J4.4, R11.1, U4.U3 (CCLK)
CFG0: R5.1, U4.U4 (CFG_0)
DONE: R8.1, U4.Y3 (DONE)
DS0: J1.3, U4.B18 (PT62B)
DS1: J1.13, U4.A12 (PT40A)
DS2: J1.14, U4.B11 (PT29A/PCLKT0_0)
DS3: J1.15, U4.A11 (PT27B/PCLKC0_1)
DS4: J1.23, U4.A9 (PT24A/GR_PCLK0_1)
DS5: J1.24, U4.A8 (PT18B)
DS6: J1.25, U4.A7 (PT18A)
DS7: J1.26, U4.B6 (PT4B)
DS8: J1.27, U4.A6 (PT4A)
DS9: J1.28, U4.A5 (PL2B)
DS10: J1.31, U4.B4 (PL5B)
DS11: J1.32, U4.A4 (PL2A)
DS12: J1.33, U4.A3 (PL5C)
DS13: J1.34, U4.B2 (PL14C/VREF1_7)
DS14: J1.35, U4.A2 (PL14A)
DS15: J1.36, U4.B1 (PL14B)
DS_CLK: J1.22, U4.B12 (PT35A/PCLKT1_0)
FB_1V1: R1.2, R2.1, U1.5 (FB)
FB_1V1_SD: R3.2, R4.1, U2.5 (FB)
GND: C1.2, C2.2, C3.2, C4.2, C5.2, C6.2, C7.2, C8.2, C9.2, C10.2, C11.2, C12.2, C13.2, C14.2, C15.2, C16.2, C17.2, C18.2, C19.2, C20.2, C21.2, C22.2, C23.2, C24.2, C25.2, C26.2, C27.2, C28.2, C29.2, C30.2, C31.2, C32.2, C33.2, C34.2, C35.2, C36.2, C37.2, C38.2, C39.2, C40.2, C41.2, C42.2, C43.2, C44.2, C45.2, C46.2, C47.2, C48.2, C49.2, C50.2, C51.2, C52.2, C53.2, C54.2, C55.2, C56.2, C57.2, C58.2, C59.2, C60.2, C61.2, C62.2, C63.2, C64.2, C65.2, C66.2, C67.2, C68.2, C69.2, C70.2, C71.2, C72.2, C73.2, C74.2, C75.2, J1.12, J1.30, J2.6, J3.1 (VeeT), J3.10 (VeeR), J3.11 (VeeR), J3.14 (VeeR), J3.17 (VeeT), J3.20 (VeeT), J3.CAGE, J4.1, J4.8, R2.2, R4.2, R14.2, R17.2, U1.2 (GND), U2.2 (GND), U3.2 (GND), U4.B7 (GND), U4.B14 (GND), U4.C19 (GND), U4.D4 (GND), U4.F7 (GND), U4.F8 (GND), U4.F13 (GND), U4.F14 (GND), U4.G4 (GND), U4.G6 (GND), U4.G7 (GND), U4.G8 (GND), U4.G9 (GND), U4.G10 (GND), U4.G11 (GND), U4.G12 (GND), U4.G13 (GND), U4.G14 (GND), U4.G15 (GND), U4.G17 (GND)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
HOLDN: R10.1, U4.R2 (PB15A/HOLDN/DI/BUSY/CSSPIN/CEN)
INITN: R7.1, U4.V3 (INITN)
IRQ: J1.21, R20.1, U5.1 (~INT)
MISO: J1.40, J4.6, R15.1, U4.V2 (PB11A/D1/MISO/IO1)
MOSI: J1.39, J4.5, U4.W2 (PB11B/D0/MOSI/IO0)
OLT_PROGRAMN: R6.1, U4.W3 (PROGRAMN), U5.13 (IO1_0)
ONU_PROGRAMN: J4.7, U5.14 (IO1_1)
ONU_SCL: J4.2, R21.1, U6.8 (SC1)
ONU_SDA: J4.3, R22.1, U6.7 (SD1)
P7_BUF: R25.1, U7.4
P7_OE_N: R23.1, U5.8 (IO0_4), U7.1
P9_BUF: R26.1, U8.4
P9_OE_N: R24.1, U5.9 (IO0_5), U8.1
REF125_OE: R17.1, U5.11 (IO0_7), Y2.1 (OE)
REF155_OE: R16.1, U5.10 (IO0_6), Y1.1 (OE)
REFCLK_N: U4.Y12 (REFCLKN_D0), Y1.5 (OUT-), Y2.5 (OUT-)
REFCLK_P: U4.Y11 (REFCLKP_D0), Y1.4 (OUT+), Y2.4 (OUT+)
RSSI_TRIG: J1.18, U8.2
RX0_N: J3.12 (RD-), U4.Y6 (HDRXN0_D0CH0)
RX0_P: J3.13 (RD+), U4.Y5 (HDRXP0_D0CH0)
RX_RESET: J1.17, U7.2
SCL: J1.19, R18.1, U5.22 (SCL), U6.1 (SCL)
SDA: J1.20, R19.1, U5.23 (SDA), U6.2 (SDA)
SFP_LOS: J3.8 (RX_LOS), R29.1, U5.6 (IO0_2)
SFP_MOD_ABS: J3.6 (MOD_ABS), R30.1, U5.4 (IO0_0)
SFP_P7: J3.7 (RS0), R25.2
SFP_P9: J3.9 (RS1), R26.2
SFP_SCL: J3.5 (SCL), R31.1, U6.5 (SC0)
SFP_SDA: J3.4 (SDA), R32.1, U6.4 (SD0)
SFP_TX_DIS: J3.3 (TX_DISABLE), R28.1, U5.7 (IO0_3)
SFP_TX_FAULT: J3.2 (TX_FAULT), R27.1, U5.5 (IO0_1)
SN: J1.38, R9.1, U4.T2 (PB13A/SN/CSN)
SW_1V1: L1.1, U1.3 (SW)
SW_1V1_SD: L2.1, U2.3 (SW)
TCK: J2.2, R14.1, U4.T5 (TCK)
TDI: J2.3, R12.1, U4.R5 (TDI)
TDO: J2.4, U4.V4 (TDO)
TMS: J2.5, R13.1, U4.U5 (TMS)
TX0_N: J3.18 (TD+), U4.W5 (HDTXN0_D0CH0)
TX0_P: J3.19 (TD-), U4.W4 (HDTXP0_D0CH0)
TX_CLK: J1.1, RN3.7 (R2.2)
TX_CLK_S: RN3.2 (R2.1), U4.B19 (PT65B)
US0: J1.2, RN3.8 (R1.2)
US0_S: RN3.1 (R1.1), U4.A19 (PT67A)
US1: J1.4, RN2.5 (R4.2)
US1_S: RN2.4 (R4.1), U4.B17 (PT60A)
US2: J1.5, RN2.6 (R3.2)
US2_S: RN2.3 (R3.1), U4.A17 (PT62A)
US3: J1.6, RN2.7 (R2.2)
US3_S: RN2.2 (R2.1), U4.B16 (PT56B)
US4: J1.7, RN2.8 (R1.2)
US4_S: RN2.1 (R1.1), U4.B15 (PT51A)
US5: J1.8, RN1.5 (R4.2)
US5_S: RN1.4 (R4.1), U4.A14 (PT47A)
US6: J1.9, RN1.6 (R3.2)
US6_S: RN1.3 (R3.1), U4.B13 (PT42A)
US7: J1.10, RN1.7 (R2.2)
US7_S: RN1.2 (R2.1), U4.A13 (PT40B)

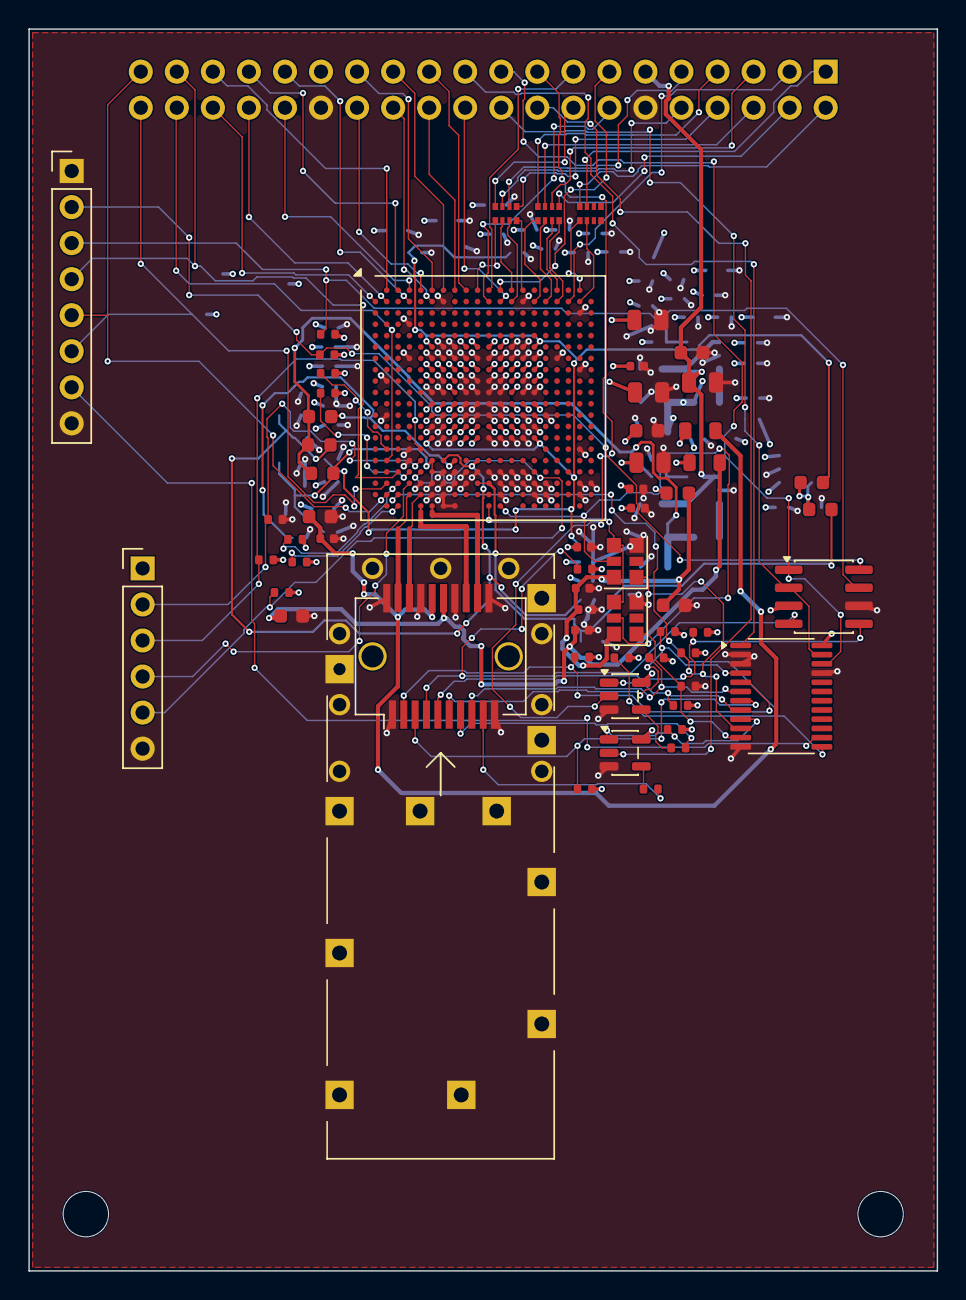
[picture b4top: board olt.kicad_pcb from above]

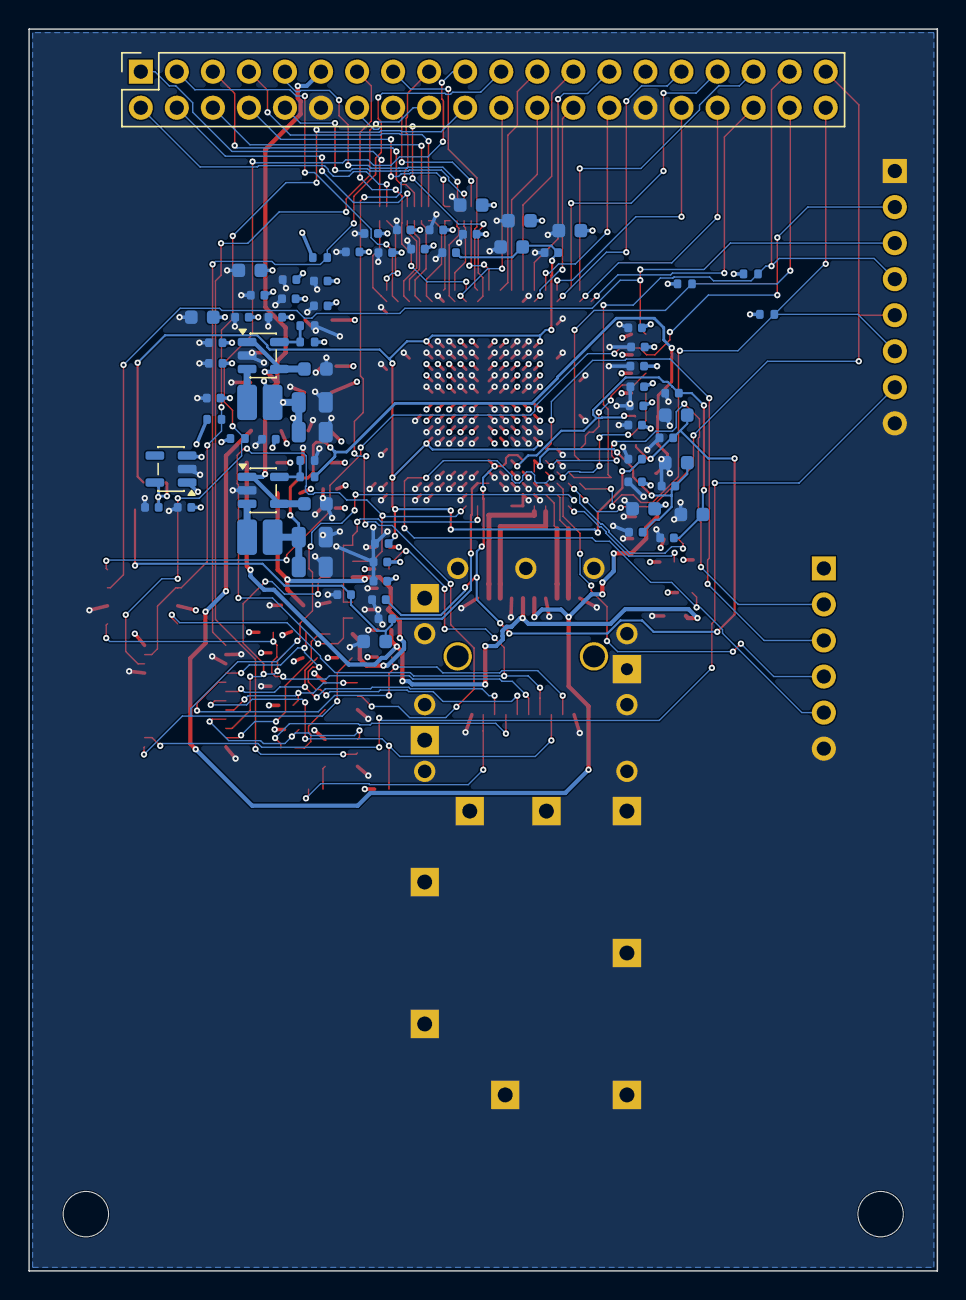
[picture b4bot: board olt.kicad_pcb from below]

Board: 4 copper layers, 64.0 x 87.5 mm, 136 parts (74 on the bottom side), 96 nets.

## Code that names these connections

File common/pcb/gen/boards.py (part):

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        cfg = {'CFG_0': 'GND', 'CFG_1': 'GND', 'CFG_2': 'GND', 'PROGRAMN': programn, 'INITN': 'INITN', 'DONE': 'DONE',
               'TCK': 'TCK', 'TDI': 'TDI', 'TDO': 'TDO', 'TMS': 'TMS', 'CCLK': spi[1]}
        cfg[f'CFG_{mode[-1]}'] = mode
        select, idle = ('HOLDN/DI/BUSY/CSSPIN/CEN', 'SN/CSN') if flash else ('SN/CSN', 'HOLDN/DI/BUSY/CSSPIN/CEN')
        dual = {select: spi[0], 'D0/MOSI/IO0': spi[2], 'D1/MISO/IO1': spi[3], idle: 'HOLDN'}
        for b, f in all_balls.items():
            if f in cfg: conn[b] = cfg[f]
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          {'A': 'ONU_BEN_P', 'B': 'ONU_BEN_N', 'R': 'LD_BEN', 'VCC': '+3V3_OPT', 'GND': 'GND'}, MPN='SN65LVDT2DBVR')
    b.decouple('+3V3_OPT', 1)
    b.r('6.2k', 'LD_BEN_N', 'GND')    # BEN- threshold for LVTTL on BEN+ (datasheet Fig. 2e)
    for pin, r_gnd, dac in (('APCSET', '20k', 'APC_ADJ'), ('MODSET', '12k', 'MOD_ADJ')):
        b.r(r_gnd, pin, 'GND'); b.r('10k', pin, dac)
    b.r('5.6k', 'BIASMAX', 'GND')
    b.r('3.9k', 'MODMON', 'GND'); b.r('1.5k', 'BIASMON', 'GND'); b.r('1k', 'RSSI', 'GND')   # <= 2.5 V ADC, RSSI < 1.2 V
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    b.r(r_top, f'{p}HV_OUT', f'{p}APD_FB', fp='Resistor_SMD:R_0603_1608Metric')   # 0603: 55 V across it
    b.r('10k', f'{p}APD_FB', 'GND'); b.r('20k', f'{p}APD_FB', f'{p}APD_ADJ')
    b.r('39k', f'{p}APD_ISHORT', 'GND')   # 2.6 mA limit (100 / kOhm): under an APD's 3 mA maximum, over the host's 2 mA cut
    b.c('10n', f'{p}APD_CAP', **hv)       # CAP sits at the output voltage (85 V pin; TI's EVM: 4.7 nF 100 V)
    b.r('10', f'+3V3_{p}APD', f'+3V3_{p}APDA'); b.c('2.2u', f'+3V3_{p}APDA')
    b.r('1.5k', f'{p}APD_MON', 'GND'); b.c('10p', f'{p}APD_MON')     # 4:5 mirror: 2 mA APD -> 2.4 V
    b.r('3.01k', f'{p}APD_MON2', 'GND'); b.c('10p', f'{p}APD_MON2')
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    return b

def sfp_cage(b, name, td, rd, vcc='+3V3'):
    """SFP/SFP+ cage, own I2C bus; RS0/RS1 (OLT modules: Rx_Reset / RSSI trigger, 330 ohm for old pin-9-grounded modules)
    through series R so the FPGA keeps them hi-Z until the module is identified."""
    b.block = f'sfp:{name}'
    t, r = f'+3V3_{name}T', f'+3V3_{name}R'
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
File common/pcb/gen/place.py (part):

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def laser_cell(lay, driver, p, port):
    """The laser current's parts between the driver's output pins and the TX can: the series resistors in a row south
    of their pins, each dummy-load diode beside its resistor; the input pair's termination north of its pins; the three
    current-setting resistors at their pins (IMAX east, MODSET / BIASSET west). Their tracks are laid here: straight,
    and clear of the via each VCC pin between them needs."""
    def wire(net, r, x, y, toward, jog):
        pin = pad_of_net(lay, driver, net)
        lay.place_pad(r, next(n for n, v in lay.parts[r].conns.items() if v == net), x, y, toward)
        lay.track(net, [pin, (pin[0], y - jog), (x, y)], lay.bd.serdes_w, pcbnew.B_Cu)
    for pin, dx, dy, toward in (('IMAX', 1.5, 0, (0, 1)), ('MODSET', -1.0, 0.2, (-1, 0)), ('BIASSET', -1.0, -0.2, (-1, 0))):
        net = f'{p}LD_{pin}'
        (x, y), r = pad_of_net(lay, driver, net), part_on(lay, net, 'R')
        lay.place_pad(r, next(n for n, v in lay.parts[r].conns.items() if v == net), x + dx, y + dy, toward)
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    u = refs(lay, 'SY88236L')[0]
    pin = lambda n: lay.pad_xy(u, n)
    cap = lambda net: pad_of_net(lay, part_on(lay, net, 'C'), net)
    tp, tn, a, b = cap('ONU_TD_P'), cap('ONU_TD_N'), pin('7'), pin('6')
    hand_pair(lay, 'ONU_TD_P', [tp, (tp[0], a[1] - 1.0), (tp[0] + 1.0, a[1]), (a[0] - 0.6, a[1]), a], 1)
    hand_pair(lay, 'ONU_TD_N', [tn, (tn[0], a[1] - 2.0), (tn[0] + 1.0, a[1] - 1.0), (b[0] - 1.3, a[1] - 1.0), (b[0] - 0.8, b[1]), b], 2)
    rp, rn, c, d = cap('ONU_RD_P'), cap('ONU_RD_N'), pin('31'), pin('30')
    yp, yn = rp[1] + 1.5, rn[1] + 1.1
    hand_pair(lay, 'ONU_RD_P', [rp, (rp[0], yp), (rp[0] + c[1] - 1.56 - yp, c[1] - 1.56), (c[0], c[1] - 1.56), c], 1)
    hand_pair(lay, 'ONU_RD_N', [rn, (rn[0], yn), (rn[0] + c[1] - 2.56 - yn, c[1] - 2.56), (d[0], c[1] - 2.56), d], 1)
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
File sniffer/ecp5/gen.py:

#!/usr/bin/env python3
# SPDX-License-Identifier: CERN-OHL-S-2.0
"""Writes the ECP5 build inputs derived from code: dcu_params.vh (the DCUA parameters, one table for both lanes)
and sniffer.lpf (every pin's ball read from the routed card). Usage: gen.py <board.kicad_pcb> <out dir>"""
import re
import sys

# 2.48832 Gb/s from the 155.52 MHz VCXO: x16, no divider; 20-bit words (1:2 gear) at 124.416 MHz.
# Values after LiteICLink's serdes_ecp5.py (10BSER, hardware-proven), raw: no 8b10b, comma, word aligner or CTC.
DUAL = {
    'D_MACROPDB': '0b1', 'D_IB_PWDNB': '0b1', 'D_TXPLL_PWDNB': '0b1',
    'D_REFCK_MODE': '0b010', 'D_TX_MAX_RATE': '2.5', 'D_TX_VCO_CK_DIV': '0b000',
    'D_BITCLK_LOCAL_EN': '0b1',
    'D_CMUSETBIASI': '0b00', 'D_CMUSETI4CPP': '0d3', 'D_CMUSETI4CPZ': '0d3', 'D_CMUSETI4VCO': '0b00',
    'D_CMUSETICP4P': '0b01', 'D_CMUSETICP4Z': '0b101', 'D_CMUSETINITVCT': '0b00', 'D_CMUSETISCL4VCO': '0b000',
    'D_CMUSETP1GM': '0b000', 'D_CMUSETP2AGM': '0b000', 'D_CMUSETZGM': '0b000', 'D_SETIRPOLY_AUX': '0b01',
    'D_SETICONST_AUX': '0b01', 'D_SETIRPOLY_CH': '0b01', 'D_SETICONST_CH': '0b10', 'D_SETPLLRC': '0d1',
    'D_RG_EN': '0b0', 'D_RG_SET': '0b00', 'D_REQ_ISET': '0b011', 'D_PD_ISET': '0b11',
    'D_LOW_MARK': '0d4', 'D_HIGH_MARK': '0d12',
}
LANE = {
    'PROTOCOL': '10BSER', 'UC_MODE': '0b1', 'ENC_BYPASS': '0b1', 'DEC_BYPASS': '0b1', 'CTC_BYPASS': '0b1',
    'LSM_DISABLE': '0b1', 'ENABLE_CG_ALIGN': '0b0', 'WA_BYPASS': '0b1',
    'RPWDNB': '0b1', 'REQ_EN': '0b0', 'RX_RATE_SEL': '0d10', 'RTERM_RX': '0d19', 'RXIN_CM': '0b11',
    'RXTERM_CM': '0b11', 'CDR_MAX_RATE': '2.5', 'RX_DCO_CK_DIV': '0b000', 'RX_GEAR_MODE': '0b1',
    'FF_RX_H_CLK_EN': '0b1', 'FF_RX_F_CLK_DIS': '0b1', 'SEL_SD_RX_CLK': '0b1',
    'AUTO_FACQ_EN': '0b1', 'AUTO_CALIB_EN': '0b1', 'PDEN_SEL': '0b1',  # phase detector off on LOS
    'DCOATDCFG': '0b00', 'DCOATDDLY': '0b00', 'DCOBYPSATD': '0b1', 'DCOCALDIV': '0b000', 'DCOCTLGI': '0b011',
    'DCODISBDAVOID': '0b0', 'DCOFLTDAC': '0b00', 'DCOFTNRG': '0b001', 'DCOIOSTUNE': '0b010', 'DCOITUNE': '0b00',
    'DCOITUNE4LSB': '0b010', 'DCOIUPDNX2': '0b1', 'DCONUOFLSB': '0b100', 'DCOSCALEI': '0b01',
    'DCOSTARTVAL': '0b010', 'DCOSTEP': '0b11',
    'RLOS_SEL': '0b1', 'RX_LOS_EN': '0b1', 'RX_LOS_LVL': '0b100', 'RX_LOS_CEQ': '0b11',
    # TX: only CH0's, for its clock (the VCXO domain); the pins are open on the card
    'TPWDNB': '0b0', 'TX_GEAR_MODE': '0b1', 'FF_TX_H_CLK_EN': '0b1', 'FF_TX_F_CLK_DIS': '0b1',
    'RTERM_TX': '0d19', 'TXAMPLITUDE': '0d400',
}
PER_LANE = {0: {'TPWDNB': '0b1'}, 1: {}}
# a transmitter in use, after LiteICLink: slices 0, 2 and 3 on the main data
TX_ON = {'TPWDNB': '0b1', 'TDRV_SLICE0_CUR': '0b011', 'TDRV_SLICE0_SEL': '0b01', 'TDRV_SLICE1_CUR': '0b000',
         'TDRV_SLICE1_SEL': '0b00', 'TDRV_SLICE2_CUR': '0b11', 'TDRV_SLICE2_SEL': '0b01', 'TDRV_SLICE3_CUR': '0b10',
         'TDRV_SLICE3_SEL': '0b01', 'TDRV_SLICE4_CUR': '0b00', 'TDRV_SLICE4_SEL': '0b00', 'TDRV_SLICE5_CUR': '0b00',
         'TDRV_SLICE5_SEL': '0b00'}

PINS = re.compile(r'^(FWD_CLK|DS\d+|US\d+)_S$|^(VCXO_PWM|DS_SD)$')
SERDES = ['DS_RX_P', 'DS_RX_N', 'US_RX_P', 'US_RX_N', 'REFCLK_P', 'REFCLK_N'] # dedicated pads: no IO type


def board_pins(pcb, wanted=lambda net: PINS.match(net) or net in SERDES):
    """ECP5 ball of each wanted net, from the footprint with the LFE5UM value."""
    text = open(pcb).read()
    at = text.find('LFE5UM')
    if at < 0:
        sys.exit(f'{pcb}: no LFE5UM footprint')
    start = text.rfind('(footprint ', 0, at)
    depth, end = 0, start
    for end in range(start, len(text)):
        depth += {'(': 1, ')': -1}.get(text[end], 0)
        if depth == 0:
            break
    pads = re.findall(r'\(pad "([A-Z0-9]+)".*?\(net (?:\d+ )?"([^"]+)"\)', text[start:end], re.S)
    return {net: ball for ball, net in pads if wanted(net)}


def port(net):
    """Top-level port of a net: DS3_S -> DS_S[3]."""
    m = re.match(r'^(DS|US)(\d+)_S$', net)
    return f'{m[1]}_S[{m[2]}]' if m else net


def write_params(out, per_lane):
    """dcu_params.vh: the shared tables, then each lane's own settings."""
    params = dict(DUAL)
    for lane, extra in per_lane.items():
        params.update({f'CH{lane}_{k}': v for k, v in dict(LANE, **extra).items()})
    with open(f'{out}/dcu_params.vh', 'w') as f:
        f.write(',\n'.join(f'  .{k}("{v}")' for k, v in params.items()) + '\n')


def main(pcb, out):
    pins = board_pins(pcb)
    want = ['FWD_CLK_S', 'VCXO_PWM', 'DS_SD'] + [f'DS{i}_S' for i in range(16)] + [f'US{i}_S' for i in range(8)]
    missing = [n for n in want + SERDES if n not in pins]
    if missing:
        sys.exit(f'{pcb}: no ECP5 ball for {missing}')
    with open(f'{out}/sniffer.lpf', 'w') as f:
        for net in want:
            f.write(f'LOCATE COMP "{port(net)}" SITE "{pins[net]}";\n')
            f.write(f'IOBUF PORT "{port(net)}" IO_TYPE=LVCMOS33;\n')
        for net in SERDES:
            f.write(f'LOCATE COMP "{net}" SITE "{pins[net]}";\n')
        f.write('FREQUENCY NET "ref_clk" 124.416 MHZ;\nFREQUENCY NET "ds_clk" 124.416 MHZ;\n'
                'FREQUENCY NET "out_clk" 77.76 MHZ;\n')
    write_params(out, PER_LANE)


if __name__ == '__main__':
    if len(sys.argv) != 3:
        sys.exit(__doc__)
    main(*sys.argv[1:])
